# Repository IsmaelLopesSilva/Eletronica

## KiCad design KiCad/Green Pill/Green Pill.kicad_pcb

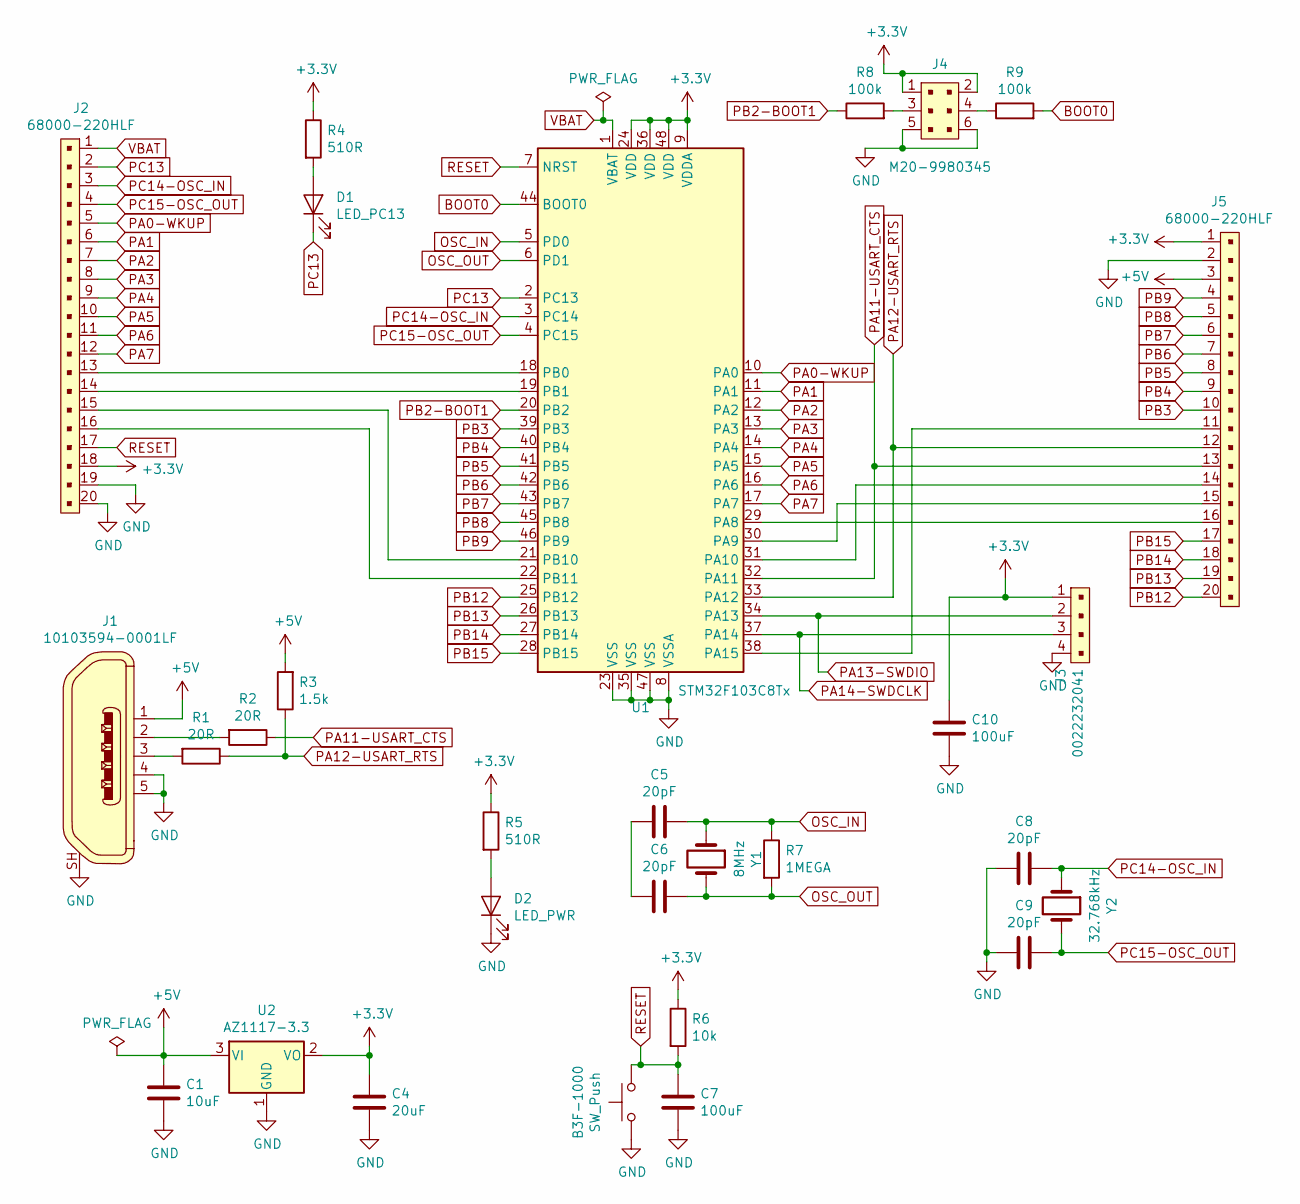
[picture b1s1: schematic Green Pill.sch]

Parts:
B3F-1000: SW_Push; SW_PUSH_6mm_H4.3mm
C1: 10uF; CP_Radial_D6.3mm_P2.50mm
C4: 20uF; CP_Radial_D6.3mm_P2.50mm
C5, C6, C8, C9: 20pF; C_Disc_D5.0mm_W2.5mm_P5.00mm
C7, C10: 100uF; CP_Radial_D6.3mm_P2.50mm
D1: LED_PC13; LED_D3.0mm
D2: LED_PWR; LED_D3.0mm
J1: 10103594-0001LF; USB_Micro_B_Female_10118194-0001LF; MPN 10103594-0001LF; Digi-Key_PN 609-4050-1-ND
J2, J5: 68000-220HLF; PinSocket_1x20_P2.54mm_Vertical; MPN 68000-220HLF; Digi-Key_PN 609-5100-ND
J3: 0022232041; PinHeader_1x4_P2.54mm_Drill1.02mm; MPN 0022232041; Digi-Key_PN WM4202-ND
J4: M20-9980345; PinHeader_2x03_P2.54mm_Vertical; MPN M20-9980345; Digi-Key_PN 952-2120-ND
R1, R2: 20R; R_Axial_DIN0207_L6.3mm_D2.5mm_P7.62mm_Horizontal
R3: 1.5k; R_Axial_DIN0207_L6.3mm_D2.5mm_P7.62mm_Horizontal
R4, R5: 510R; R_Axial_DIN0207_L6.3mm_D2.5mm_P7.62mm_Horizontal
R6: 10k; R_Axial_DIN0207_L6.3mm_D2.5mm_P7.62mm_Horizontal
R7: 1MEGA; R_Axial_DIN0207_L6.3mm_D2.5mm_P7.62mm_Horizontal
R8, R9: 100k; R_Axial_DIN0207_L6.3mm_D2.5mm_P7.62mm_Horizontal
U1: STM32F103C8Tx; LQFP-48_7x7mm_P0.5mm
U2: AZ1117-3.3; SOT-223
Y1: 8MHz; Crystal_HC18-U_Vertical
Y2: 32.768kHz; Crystal_AT310_D3.0mm_L10.0mm_Vertical

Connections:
+3V3: C4.1, C10.1, J2.18, J3.1, J4.1, J4.2, J5.1, R4.1, R5.1, R6.1, U1.9 (VDDA), U1.24 (VDD), U1.36 (VDD), U1.48 (VDD), U2.2 (VO)
+5V: C1.1, J1.1, J5.3, R3.2, U2.3 (VI)
BOOT0: R9.2, U1.44 (BOOT0)
GND: B3F-1000.1, C1.2, C4.2, C7.2, C8.2, C9.2, C10.2, D2.1 (K), J1.4, J1.5, J1.SH, J2.19, J2.20, J3.4, J4.5, J4.6, J5.2, U1.8 (VSSA), U1.23 (VSS), U1.35 (VSS), U1.47 (VSS), U2.1 (GND); also elsewhere on the board
unnamed: C5.2, C6.2
unnamed: D1.2 (A), R4.2
unnamed: D2.2 (A), R5.2
unnamed: J1.2, R2.2
unnamed: J1.3, R1.2
unnamed: J2.13, U1.18 (PB0)
unnamed: J2.14, U1.19 (PB1)
unnamed: J2.15, U1.21 (PB10)
unnamed: J2.16, U1.22 (PB11)
unnamed: J4.3, R8.2
unnamed: J4.4, R9.1
unnamed: J5.11, U1.38 (PA15)
unnamed: J5.14, U1.31 (PA10)
unnamed: J5.15, U1.30 (PA9)
unnamed: J5.16, U1.29 (PA8)
OSC_IN: C5.1, R7.1, U1.5 (PD0), Y1.1
OSC_OUT: C6.1, R7.2, U1.6 (PD1), Y1.2
PA0-WKUP: J2.5, U1.10 (PA0)
PA1: J2.6, U1.11 (PA1)
PA2: J2.7, U1.12 (PA2)
PA3: J2.8, U1.13 (PA3)
PA4: J2.9, U1.14 (PA4)
PA5: J2.10, U1.15 (PA5)
PA6: J2.11, U1.16 (PA6)
PA7: J2.12, U1.17 (PA7)
PA11-USART_CTS: J5.13, R2.1, U1.32 (PA11)
PA12-USART_RTS: J5.12, R1.1, R3.1, U1.33 (PA12)
PA13-SWDIO: J3.2, U1.34 (PA13)
PA14-SWDCLK: J3.3, U1.37 (PA14)
PB2-BOOT1: R8.1, U1.20 (PB2)
PB3: J5.10, U1.39 (PB3)
PB4: J5.9, U1.40 (PB4)
PB5: J5.8, U1.41 (PB5)
PB6: J5.7, U1.42 (PB6)
PB7: J5.6, U1.43 (PB7)
PB8: J5.5, U1.45 (PB8)
PB9: J5.4, U1.46 (PB9)
PB12: J5.20, U1.25 (PB12)
PB13: J5.19, U1.26 (PB13)
PB14: J5.18, U1.27 (PB14)
PB15: J5.17, U1.28 (PB15)
PC13: D1.1 (K), J2.2, U1.2 (PC13)
PC14-OSC_IN: C8.1, J2.3, U1.3 (PC14), Y2.1
PC15-OSC_OUT: C9.1, J2.4, U1.4 (PC15), Y2.2
RESET: B3F-1000.2, C7.1, J2.17, R6.2, U1.7 (NRST); also elsewhere on the board
VBAT: J2.1, U1.1 (VBAT)

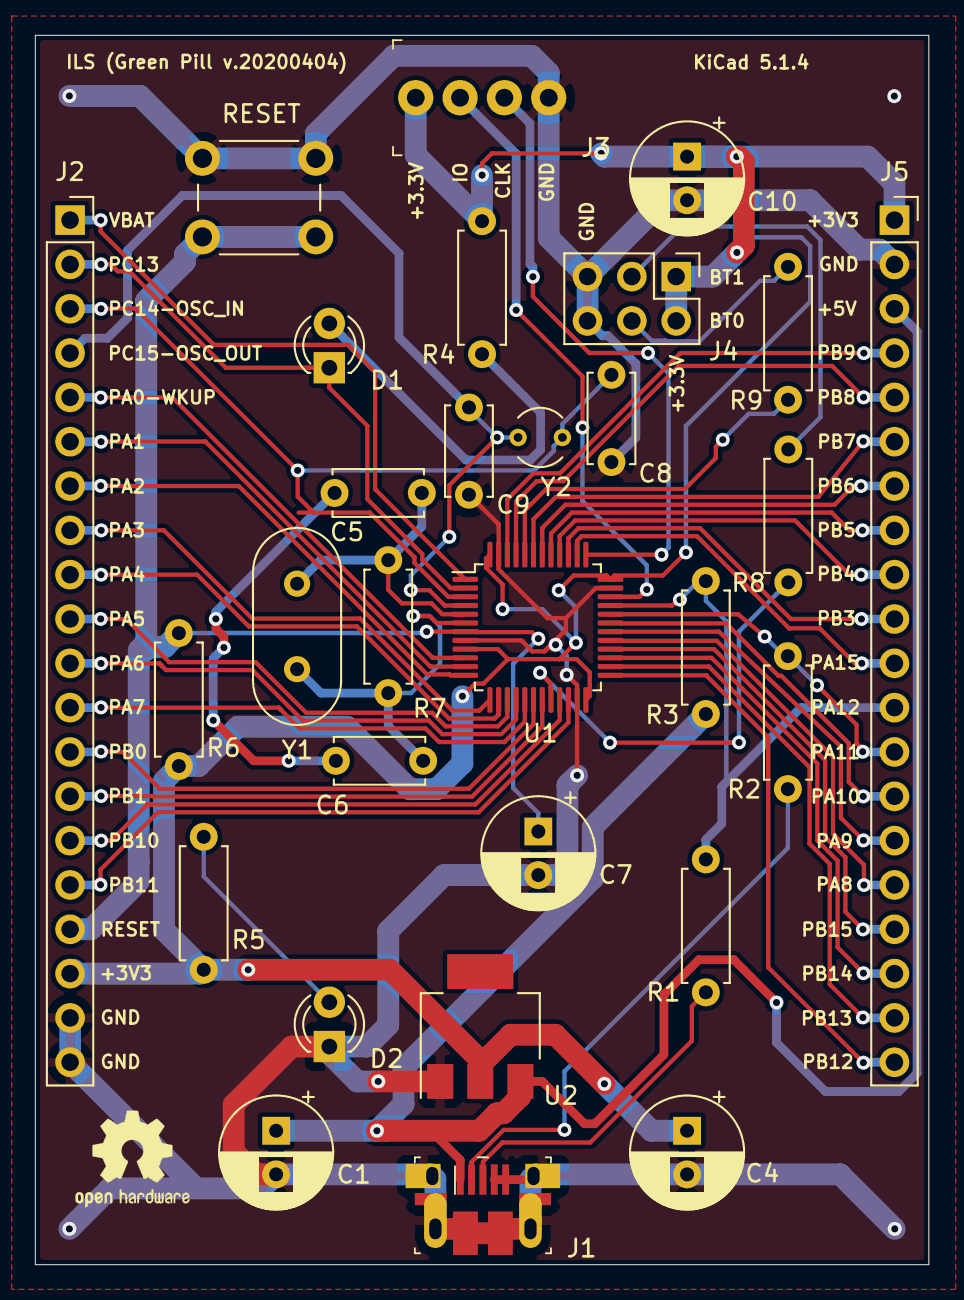
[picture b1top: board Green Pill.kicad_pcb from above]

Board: 2 copper layers, 51.2 x 70.4 mm, 29 parts (0 on the bottom side), 50 nets.

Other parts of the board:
RESET: SW_Push; SW_PUSH_6mm_H4.3mm

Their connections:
GND: RESET.1; also elsewhere on the board
RESET: RESET.2; also elsewhere on the board

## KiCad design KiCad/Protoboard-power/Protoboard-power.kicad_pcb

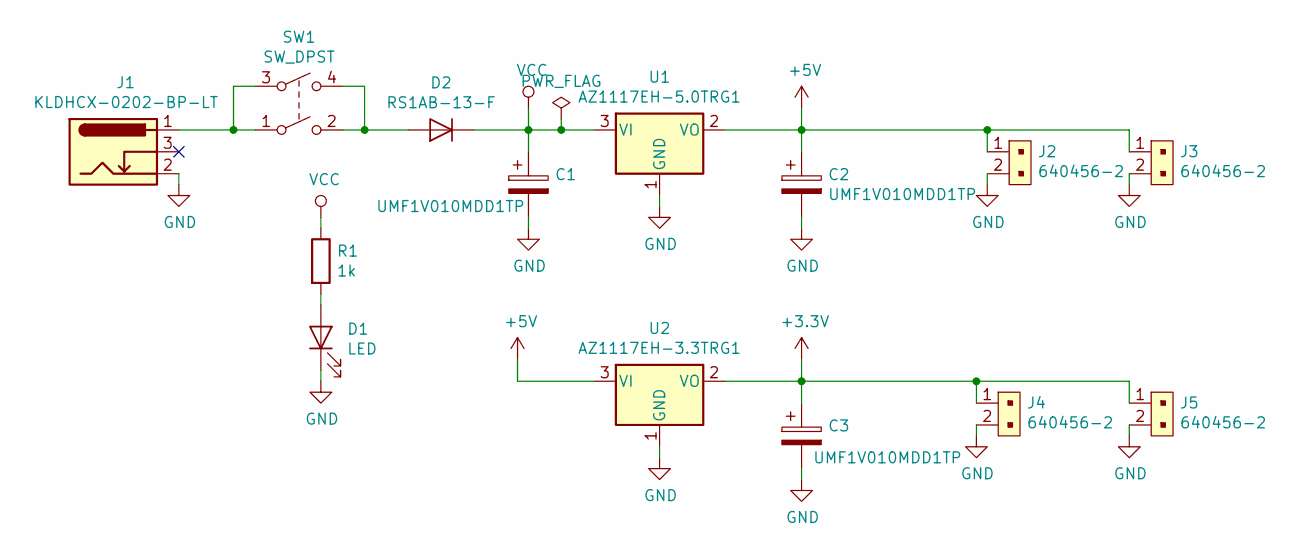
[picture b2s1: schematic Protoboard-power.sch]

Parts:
C1, C2, C3: UMF1V010MDD1TP; CP_Radial_D4.0mm_P1.50mm
D1: LED; LED_D3.0mm
D2: RS1AB-13-F; D_SMB
J1: KLDHCX-0202-BP-LT; BarrelJack_CUI_PJ-102AH_Horizontal
J2, J3, J4, J5: 640456-2; PinHeader_1x02_P2.54mm_Vertical; MPN 640456-2; Digi-Key_PN A1921-ND
R1: 1k; R_Axial_DIN0207_L6.3mm_D2.5mm_P10.16mm_Horizontal
SW1: SW_DPST; SW_PUSH_DPST_6mm_H5mm
U1: AZ1117EH-5.0TRG1; SOT-223
U2: AZ1117EH-3.3TRG1; SOT-223

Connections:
+3V3: C3.1, J4.1, J5.1, U2.2 (VO)
+5V: C2.1, J2.1, J3.1, U1.2 (VO), U2.3 (VI)
GND: C1.2, C2.2, C3.2, D1.1 (K), J1.2, J2.2, J3.2, J4.2, J5.2, U1.1 (GND), U2.1 (GND)
unnamed: D1.2 (A), R1.2
unnamed: D2.2 (A), SW1.2, SW1.4
unnamed: J1.1, SW1.1, SW1.3
VCC: C1.1, D2.1 (K), R1.1, U1.3 (VI)

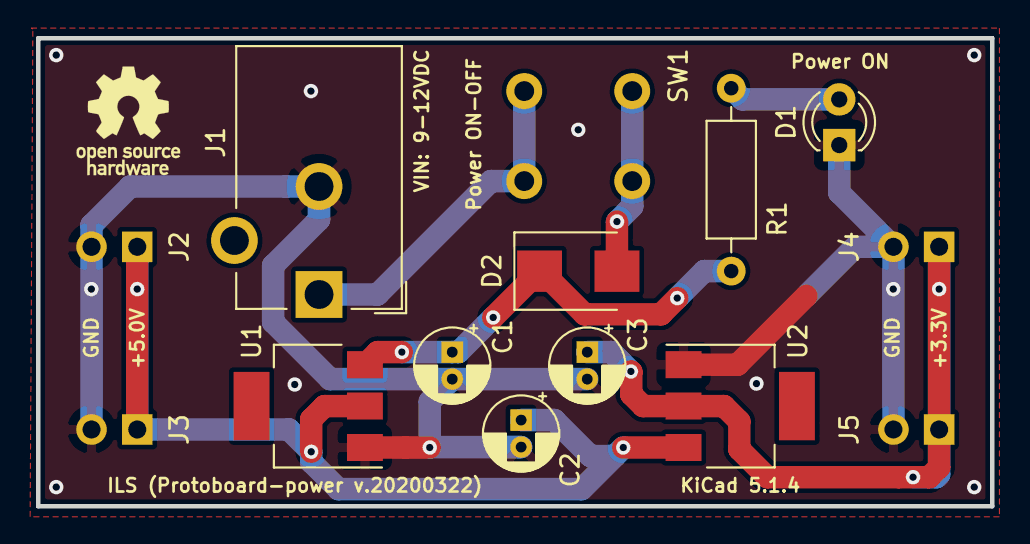
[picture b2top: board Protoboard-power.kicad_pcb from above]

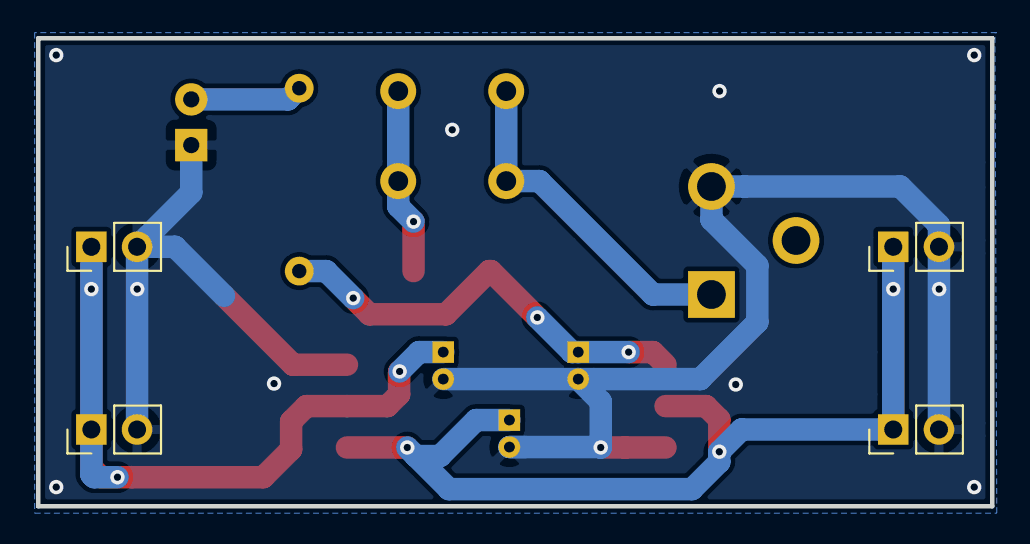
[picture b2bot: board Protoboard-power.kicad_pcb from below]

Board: 2 copper layers, 53.0 x 26.0 mm, 14 parts (4 on the bottom side), 7 nets.

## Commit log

2019-11-10 Adicionando os primeiros arquivos e dirtetórios
2019-11-10 Adicionei outros ebooks
2019-12-23 Adicionei tutoriais
2019-12-24 adicionei um arquivo
2019-12-24 adicionei cinco ebooks
2019-12-24 adicionei um ebooks
2019-12-28 Adicionei arquivos
2019-12-28 adicionei arquivo
2019-12-31 Adicionei pastas e arquivos
2020-01-04 renomeie e adicionei arquivos
2020-03-07 Adicionei diretorio e arquivo
2020-03-27 adicionei novo projeto
2020-03-29 adicionado arquivos
2020-04-04 adicionei projeto
2020-04-05 corrigi o projeto
2020-04-05 organizei os arquivos
